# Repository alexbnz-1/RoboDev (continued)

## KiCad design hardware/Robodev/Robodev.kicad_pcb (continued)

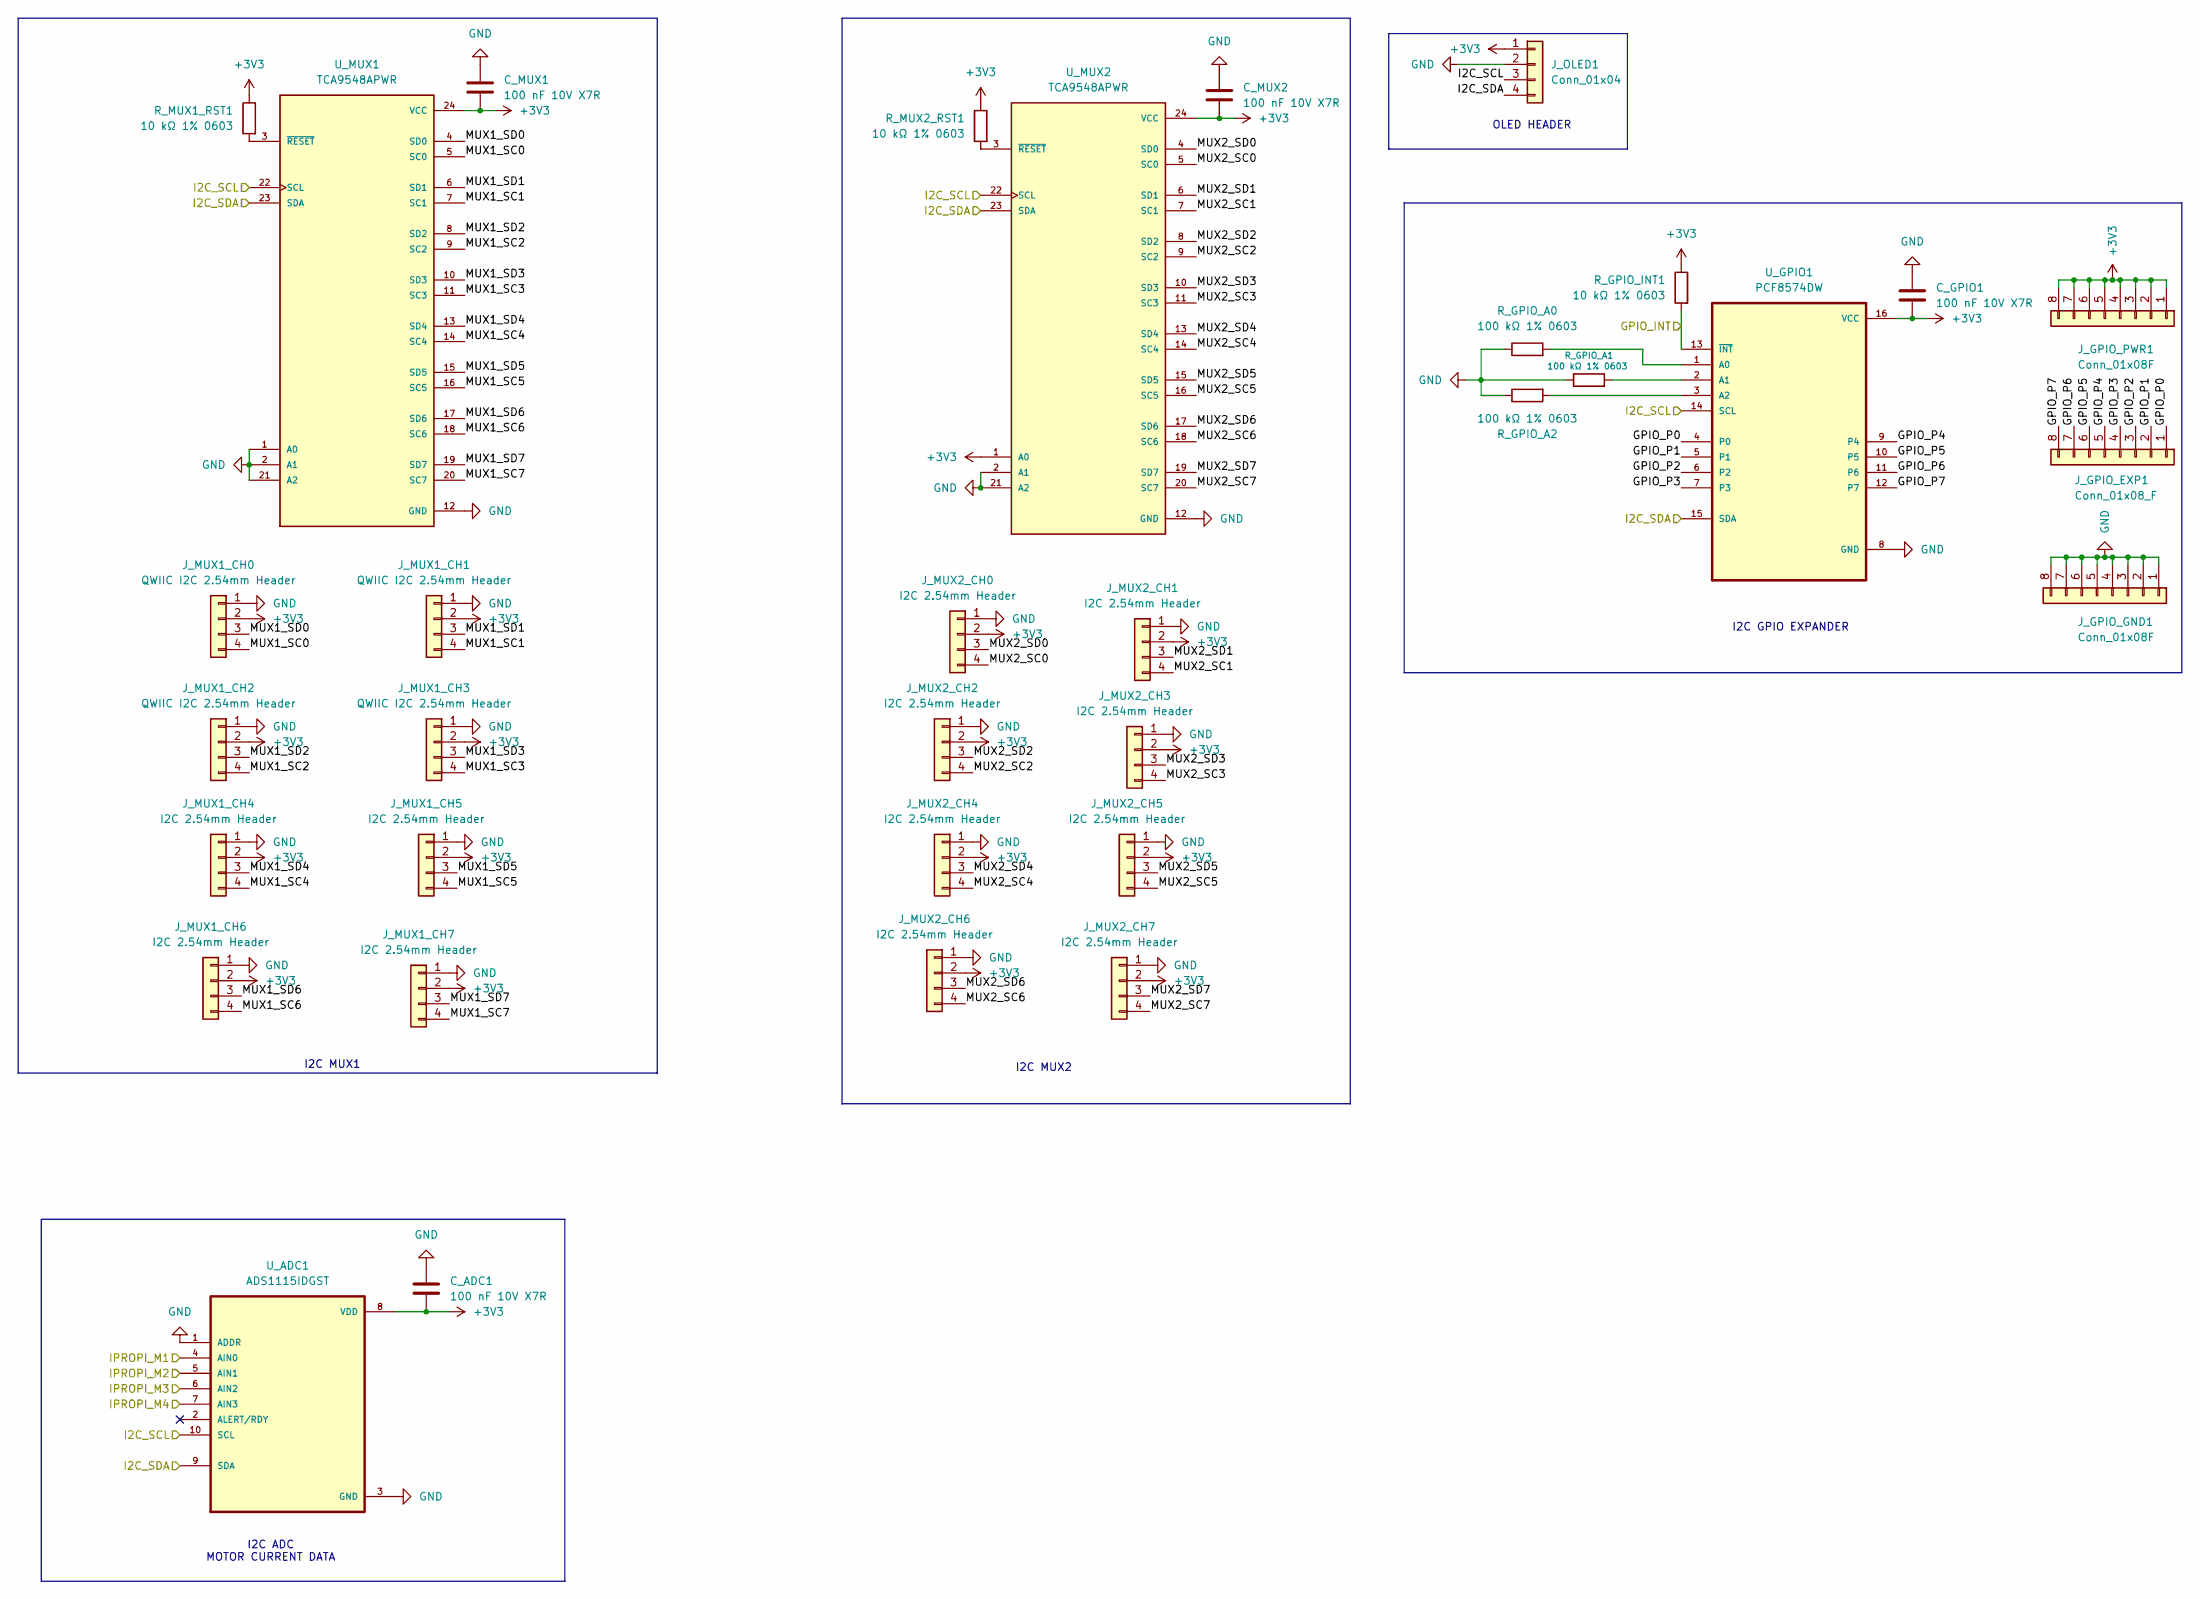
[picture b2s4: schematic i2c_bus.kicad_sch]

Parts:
C_ADC1: 100 nF 10V X7R; C_0603_1608Metric
C_GPIO1: 100 nF 10V X7R; C_0603_1608Metric
C_MUX1, C_MUX2: 100 nF 10V X7R; C_0603_1608Metric
J_GPIO_EXP1: Conn_01x08_F; PinSocket_1x08_P2.54mm_Vertical
J_GPIO_GND1: Conn_01x08F; PinSocket_1x08_P2.54mm_Vertical
J_GPIO_PWR1: Conn_01x08F; PinSocket_1x08_P2.54mm_Vertical
J_MUX1_CH0, J_MUX1_CH1, J_MUX1_CH2, J_MUX1_CH3: QWIIC I2C 2.54mm Header; ADAFRUIT_4328
J_MUX1_CH4, J_MUX1_CH5, J_MUX1_CH6, J_MUX1_CH7, J_MUX2_CH0, J_MUX2_CH1, J_MUX2_CH2, J_MUX2_CH3, J_MUX2_CH4, J_MUX2_CH5, J_MUX2_CH6, J_MUX2_CH7: I2C 2.54mm Header; PinHeader_1x04_P2.54mm_Vertical
J_OLED1: Conn_01x04; PinSocket_1x04_P2.54mm_Vertical
R_GPIO_A0, R_GPIO_A1, R_GPIO_A2: 100 kΩ 1% 0603; R_0603_1608Metric
R_GPIO_INT1: 10 kΩ 1% 0603; R_0603_1608Metric
R_MUX1_RST1, R_MUX2_RST1: 10 kΩ 1% 0603; R_0603_1608Metric
U_ADC1: ADS1115IDGST; SOP50P490X110-10N
U_GPIO1: PCF8574DW; SOIC127P1030X265-16N
U_MUX1, U_MUX2: TCA9548APWR; SOP65P640X120-24N; PARTREV G

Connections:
+3V3: C_ADC1.2, C_GPIO1.2, C_MUX1.2, C_MUX2.2, J_GPIO_PWR1.1, J_GPIO_PWR1.2, J_GPIO_PWR1.3, J_GPIO_PWR1.4, J_GPIO_PWR1.5, J_GPIO_PWR1.6, J_GPIO_PWR1.7, J_GPIO_PWR1.8, J_MUX1_CH0.2, J_MUX1_CH1.2, J_MUX1_CH2.2, J_MUX1_CH3.2, J_MUX1_CH4.2, J_MUX1_CH5.2, J_MUX1_CH6.2, J_MUX1_CH7.2, J_MUX2_CH0.2, J_MUX2_CH1.2, J_MUX2_CH2.2, J_MUX2_CH3.2, J_MUX2_CH4.2, J_MUX2_CH5.2, J_MUX2_CH6.2, J_MUX2_CH7.2, J_OLED1.1, R_GPIO_INT1.1, R_MUX1_RST1.1, R_MUX2_RST1.1, U_ADC1.8 (VDD), U_GPIO1.16 (VCC), U_MUX1.24 (VCC), U_MUX2.1 (A0), U_MUX2.24 (VCC); also elsewhere on the board
/i2c_bus/GPIO_INT: R_GPIO_INT1.2, U_GPIO1.13 (~INT); also elsewhere on the board
/i2c_bus/GPIO_P0: J_GPIO_EXP1.1, U_GPIO1.4 (P0)
/i2c_bus/GPIO_P1: J_GPIO_EXP1.2, U_GPIO1.5 (P1)
/i2c_bus/GPIO_P2: J_GPIO_EXP1.3, U_GPIO1.6 (P2)
/i2c_bus/GPIO_P3: J_GPIO_EXP1.4, U_GPIO1.7 (P3)
/i2c_bus/GPIO_P4: J_GPIO_EXP1.5, U_GPIO1.9 (P4)
/i2c_bus/GPIO_P5: J_GPIO_EXP1.6, U_GPIO1.10 (P5)
/i2c_bus/GPIO_P6: J_GPIO_EXP1.7, U_GPIO1.11 (P6)
/i2c_bus/GPIO_P7: J_GPIO_EXP1.8, U_GPIO1.12 (P7)
/i2c_bus/I2C_SCL: J_OLED1.3, U_ADC1.10 (SCL), U_GPIO1.14 (SCL), U_MUX1.22 (SCL), U_MUX2.22 (SCL); also elsewhere on the board
/i2c_bus/I2C_SDA: J_OLED1.4, U_ADC1.9 (SDA), U_GPIO1.15 (SDA), U_MUX1.23 (SDA), U_MUX2.23 (SDA); also elsewhere on the board
/i2c_bus/IPROPI_M1: U_ADC1.4 (AIN0); also elsewhere on the board
/i2c_bus/IPROPI_M2: U_ADC1.5 (AIN1); also elsewhere on the board
/i2c_bus/IPROPI_M3: U_ADC1.6 (AIN2); also elsewhere on the board
/i2c_bus/IPROPI_M4: U_ADC1.7 (AIN3); also elsewhere on the board
/i2c_bus/MUX1_SC0: J_MUX1_CH0.4, U_MUX1.5 (SC0)
/i2c_bus/MUX1_SC1: J_MUX1_CH1.4, U_MUX1.7 (SC1)
/i2c_bus/MUX1_SC2: J_MUX1_CH2.4, U_MUX1.9 (SC2)
/i2c_bus/MUX1_SC3: J_MUX1_CH3.4, U_MUX1.11 (SC3)
/i2c_bus/MUX1_SC4: J_MUX1_CH4.4, U_MUX1.14 (SC4)
/i2c_bus/MUX1_SC5: J_MUX1_CH5.4, U_MUX1.16 (SC5)
/i2c_bus/MUX1_SC6: J_MUX1_CH6.4, U_MUX1.18 (SC6)
/i2c_bus/MUX1_SC7: J_MUX1_CH7.4, U_MUX1.20 (SC7)
/i2c_bus/MUX1_SD0: J_MUX1_CH0.3, U_MUX1.4 (SD0)
/i2c_bus/MUX1_SD1: J_MUX1_CH1.3, U_MUX1.6 (SD1)
/i2c_bus/MUX1_SD2: J_MUX1_CH2.3, U_MUX1.8 (SD2)
/i2c_bus/MUX1_SD3: J_MUX1_CH3.3, U_MUX1.10 (SD3)
/i2c_bus/MUX1_SD4: J_MUX1_CH4.3, U_MUX1.13 (SD4)
/i2c_bus/MUX1_SD5: J_MUX1_CH5.3, U_MUX1.15 (SD5)
/i2c_bus/MUX1_SD6: J_MUX1_CH6.3, U_MUX1.17 (SD6)
/i2c_bus/MUX1_SD7: J_MUX1_CH7.3, U_MUX1.19 (SD7)
/i2c_bus/MUX2_SC0: J_MUX2_CH0.4, U_MUX2.5 (SC0)
/i2c_bus/MUX2_SC1: J_MUX2_CH1.4, U_MUX2.7 (SC1)
/i2c_bus/MUX2_SC2: J_MUX2_CH2.4, U_MUX2.9 (SC2)
/i2c_bus/MUX2_SC3: J_MUX2_CH3.4, U_MUX2.11 (SC3)
/i2c_bus/MUX2_SC4: J_MUX2_CH4.4, U_MUX2.14 (SC4)
/i2c_bus/MUX2_SC5: J_MUX2_CH5.4, U_MUX2.16 (SC5)
/i2c_bus/MUX2_SC6: J_MUX2_CH6.4, U_MUX2.18 (SC6)
/i2c_bus/MUX2_SC7: J_MUX2_CH7.4, U_MUX2.20 (SC7)
/i2c_bus/MUX2_SD0: J_MUX2_CH0.3, U_MUX2.4 (SD0)
/i2c_bus/MUX2_SD1: J_MUX2_CH1.3, U_MUX2.6 (SD1)
/i2c_bus/MUX2_SD2: J_MUX2_CH2.3, U_MUX2.8 (SD2)
/i2c_bus/MUX2_SD3: J_MUX2_CH3.3, U_MUX2.10 (SD3)
/i2c_bus/MUX2_SD4: J_MUX2_CH4.3, U_MUX2.13 (SD4)
/i2c_bus/MUX2_SD5: J_MUX2_CH5.3, U_MUX2.15 (SD5)
/i2c_bus/MUX2_SD6: J_MUX2_CH6.3, U_MUX2.17 (SD6)
/i2c_bus/MUX2_SD7: J_MUX2_CH7.3, U_MUX2.19 (SD7)
GND: C_ADC1.1, C_GPIO1.1, C_MUX1.1, C_MUX2.1, J_GPIO_GND1.1, J_GPIO_GND1.2, J_GPIO_GND1.3, J_GPIO_GND1.4, J_GPIO_GND1.5, J_GPIO_GND1.6, J_GPIO_GND1.7, J_GPIO_GND1.8, J_MUX1_CH0.1, J_MUX1_CH1.1, J_MUX1_CH2.1, J_MUX1_CH3.1, J_MUX1_CH4.1, J_MUX1_CH5.1, J_MUX1_CH6.1, J_MUX1_CH7.1, J_MUX2_CH0.1, J_MUX2_CH1.1, J_MUX2_CH2.1, J_MUX2_CH3.1, J_MUX2_CH4.1, J_MUX2_CH5.1, J_MUX2_CH6.1, J_MUX2_CH7.1, J_OLED1.2, R_GPIO_A0.1, R_GPIO_A1.1, R_GPIO_A2.1, U_ADC1.1 (ADDR), U_ADC1.3 (GND), U_GPIO1.8 (GND), U_MUX1.1 (A0), U_MUX1.2 (A1), U_MUX1.12 (GND), U_MUX1.21 (A2), U_MUX2.2 (A1), U_MUX2.12 (GND), U_MUX2.21 (A2); also elsewhere on the board
unnamed: R_GPIO_A0.2, U_GPIO1.1 (A0)
unnamed: R_GPIO_A1.2, U_GPIO1.2 (A1)
unnamed: R_GPIO_A2.2, U_GPIO1.3 (A2)
unnamed: R_MUX1_RST1.2, U_MUX1.3 (~RESET)
unnamed: R_MUX2_RST1.2, U_MUX2.3 (~RESET)

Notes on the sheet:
OLED HEADER
I2C GPIO EXPANDER
I2C ADC MOTOR CURRENT DATA
I2C MUX2
I2C MUX1

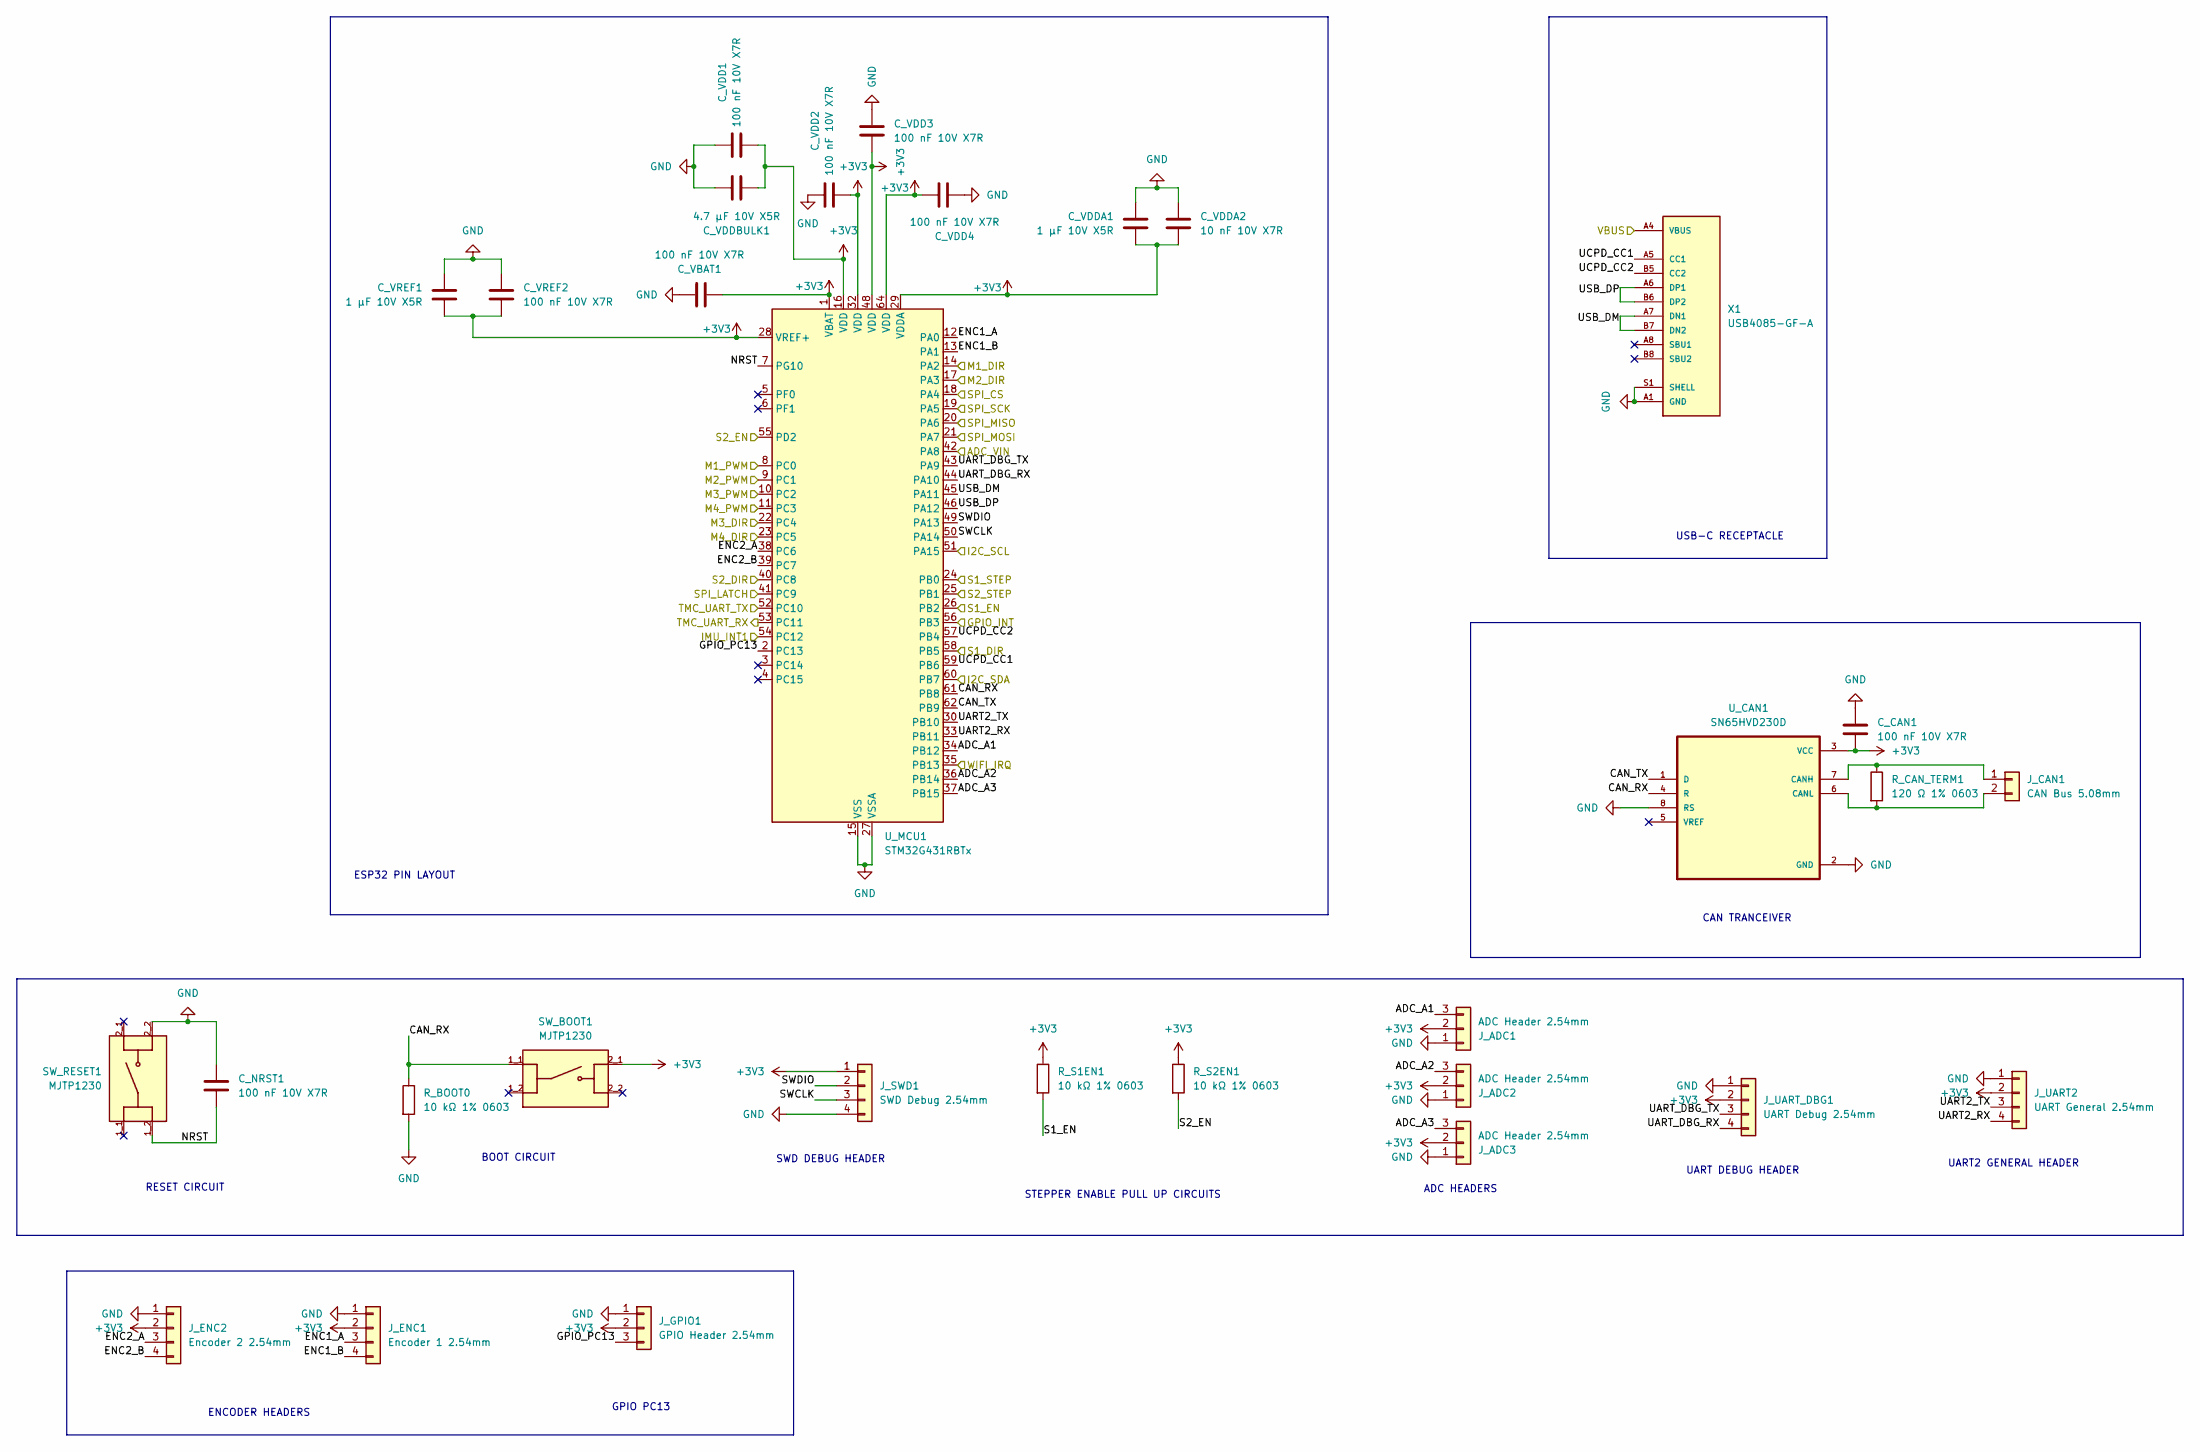
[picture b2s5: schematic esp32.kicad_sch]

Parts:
C_CAN1: 100 nF 10V X7R; C_0603_1608Metric
C_NRST1: 100 nF 10V X7R; C_0603_1608Metric
C_VBAT1: 100 nF 10V X7R; C_0603_1608Metric
C_VDD1, C_VDD2, C_VDD3, C_VDD4: 100 nF 10V X7R; C_0603_1608Metric
C_VDDA1: 1 µF 10V X5R; C_0603_1608Metric
C_VDDA2: 10 nF 10V X7R; C_0603_1608Metric
C_VDDBULK1: 4.7 µF 10V X5R; C_0603_1608Metric
C_VREF1: 1 µF 10V X5R; C_0603_1608Metric
C_VREF2: 100 nF 10V X7R; C_0603_1608Metric
J_ADC1, J_ADC2, J_ADC3: ADC Header 2.54mm; PinHeader_1x03_P2.54mm_Vertical
J_CAN1: CAN Bus 5.08mm; TerminalBlock_Phoenix_MKDS-1,5-2-5.08_1x02_P5.08mm_Horizont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
J_ENC1: Encoder 1 2.54mm; PinHeader_1x04_P2.54mm_Vertical
J_ENC2: Encoder 2 2.54mm; PinHeader_1x04_P2.54mm_Vertical
J_GPIO1: GPIO Header 2.54mm; PinSocket_1x03_P2.54mm_Vertical
J_SWD1: SWD Debug 2.54mm; FanPinHeader_1x04_P2.54mm_Vertical
J_UART2: UART General 2.54mm; PinHeader_1x04_P2.54mm_Vertical
J_UART_DBG1: UART Debug 2.54mm; PinHeader_1x04_P2.54mm_Vertical
R_BOOT0: 10 kΩ 1% 0603; R_0603_1608Metric
R_CAN_TERM1: 120 Ω 1% 0603; R_0603_1608Metric
R_S1EN1, R_S2EN1: 10 kΩ 1% 0603; R_0603_1608Metric
SW_BOOT1: MJTP1230; SW_MJTP1230; PARTREV NA
SW_RESET1: MJTP1230; SW_MJTP1230; PARTREV NA
U_CAN1: SN65HVD230D; SOIC127P599X175-8N
U_MCU1: STM32G431RBTx; LQFP-64_10x10mm_P0.5mm
X1: USB4085-GF-A; GCT_USB4085-GF-A_REVB

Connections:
+3V3: C_CAN1.2, C_VBAT1.2, C_VDD1.1, C_VDD2.1, C_VDD3.2, C_VDD4.1, C_VDDA1.2, C_VDDA2.2, C_VDDBULK1.2, C_VREF1.2, C_VREF2.2, J_ADC1.2, J_ADC2.2, J_ADC3.2, J_ENC1.2, J_ENC2.2, J_GPIO1.2, J_SWD1.1, J_UART2.2, J_UART_DBG1.2, R_S1EN1.1, R_S2EN1.1, SW_BOOT1.2_1, U_CAN1.3 (VCC), U_MCU1.1 (VBAT), U_MCU1.16 (VDD), U_MCU1.28 (VREF+), U_MCU1.29 (VDDA), U_MCU1.32 (VDD), U_MCU1.48 (VDD), U_MCU1.64 (VDD); also elsewhere on the board
/i2c_bus/GPIO_INT: U_MCU1.56 (PB3); also elsewhere on the board
/i2c_bus/I2C_SCL: U_MCU1.51 (PA15); also elsewhere on the board
/i2c_bus/I2C_SDA: U_MCU1.60 (PB7); also elsewhere on the board
/motor_dc/M1_DIR: U_MCU1.14 (PA2); also elsewhere on the board
/motor_dc/M1_PWM: U_MCU1.8 (PC0); also elsewhere on the board
/motor_dc/M2_DIR: U_MCU1.17 (PA3); also elsewhere on the board
/motor_dc/M2_PWM: U_MCU1.9 (PC1); also elsewhere on the board
/motor_dc/M3_DIR: U_MCU1.22 (PC4); also elsewhere on the board
/motor_dc/M3_PWM: U_MCU1.10 (PC2); also elsewhere on the board
/motor_dc/M4_DIR: U_MCU1.23 (PC5); also elsewhere on the board
/motor_dc/M4_PWM: U_MCU1.11 (PC3); also elsewhere on the board
/motor_stepper/S1_DIR: U_MCU1.58 (PB5); also elsewhere on the board
/motor_stepper/S1_STEP: U_MCU1.24 (PB0); also elsewhere on the board
/motor_stepper/S2_DIR: U_MCU1.40 (PC8); also elsewhere on the board
/motor_stepper/S2_STEP: U_MCU1.25 (PB1); also elsewhere on the board
/motor_stepper/TMC_UART: U_MCU1.52 (PC10), U_MCU1.53 (PC11); also elsewhere on the board
/power/ADC_VIN: U_MCU1.42 (PA8); also elsewhere on the board
/spi_bus/IMU_INT1: U_MCU1.54 (PC12); also elsewhere on the board
/spi_bus/SPI_CS: U_MCU1.18 (PA4); also elsewhere on the board
/spi_bus/SPI_LATCH: U_MCU1.41 (PC9); also elsewhere on the board
/spi_bus/SPI_MISO: U_MCU1.20 (PA6); also elsewhere on the board
/spi_bus/SPI_MOSI: U_MCU1.21 (PA7); also elsewhere on the board
/spi_bus/SPI_SCK: U_MCU1.19 (PA5); also elsewhere on the board
/spi_bus/WIFI_IRQ: U_MCU1.35 (PB13); also elsewhere on the board
/stm32/ADC_A1: J_ADC1.3, U_MCU1.34 (PB12)
/stm32/ADC_A2: J_ADC2.3, U_MCU1.36 (PB14)
/stm32/ADC_A3: J_ADC3.3, U_MCU1.37 (PB15)
/stm32/CAN_RX: R_BOOT0.1, SW_BOOT1.1_1, U_CAN1.4 (R), U_MCU1.61 (PB8)
/stm32/CAN_TX: U_CAN1.1 (D), U_MCU1.62 (PB9)
/stm32/ENC1_A: J_ENC1.3, U_MCU1.12 (PA0)
/stm32/ENC1_B: J_ENC1.4, U_MCU1.13 (PA1)
/stm32/ENC2_A: J_ENC2.3, U_MCU1.38 (PC6)
/stm32/ENC2_B: J_ENC2.4, U_MCU1.39 (PC7)
/stm32/GPIO_PC13: J_GPIO1.3, U_MCU1.2 (PC13)
/stm32/NRST: C_NRST1.2, SW_RESET1.1_2, U_MCU1.7 (PG10)
/stm32/S1_EN: R_S1EN1.2, U_MCU1.26 (PB2); also elsewhere on the board
/stm32/S2_EN: R_S2EN1.2, U_MCU1.55 (PD2); also elsewhere on the board
/stm32/SWCLK: J_SWD1.3, U_MCU1.50 (PA14)
/stm32/SWDIO: J_SWD1.2, U_MCU1.49 (PA13)
/stm32/UART2_RX: J_UART2.4, U_MCU1.33 (PB11)
/stm32/UART2_TX: J_UART2.3, U_MCU1.30 (PB10)
/stm32/UART_DBG_RX: J_UART_DBG1.4, U_MCU1.44 (PA10)
/stm32/UART_DBG_TX: J_UART_DBG1.3, U_MCU1.43 (PA9)
/stm32/UCPD_CC1: U_MCU1.59 (PB6), X1.A5 (CC1)
/stm32/UCPD_CC2: U_MCU1.57 (PB4), X1.B5 (CC2)
/stm32/USB_DM: U_MCU1.45 (PA11), X1.A7 (DN1), X1.B7 (DN2)
/stm32/USB_DP: U_MCU1.46 (PA12), X1.A6 (DP1), X1.B6 (DP2)
GND: C_CAN1.1, C_NRST1.1, C_VBAT1.1, C_VDD1.2, C_VDD2.2, C_VDD3.1, C_VDD4.2, C_VDDA1.1, C_VDDA2.1, C_VDDBULK1.1, C_VREF1.1, C_VREF2.1, J_ADC1.1, J_ADC2.1, J_ADC3.1, J_ENC1.1, J_ENC2.1, J_GPIO1.1, J_SWD1.4, J_UART2.1, J_UART_DBG1.1, R_BOOT0.2, SW_RESET1.2_2, U_CAN1.2 (GND), U_CAN1.8 (RS), U_MCU1.15 (VSS), U_MCU1.27 (VSSA), U_MCU1.31 (VSS), U_MCU1.47 (VSS), U_MCU1.63 (VSS), X1.A1 (GND), X1.A12 (GND), X1.B1 (GND), X1.B12 (GND), X1.S1 (SHELL), X1.S2 (SHELL), X1.S3 (SHELL), X1.S4 (SHELL); also elsewhere on the board
unnamed: J_CAN1.1, R_CAN_TERM1.1, U_CAN1.7 (CANH)
unnamed: J_CAN1.2, R_CAN_TERM1.2, U_CAN1.6 (CANL)
VBUS: X1.A4 (VBUS), X1.A9 (VBUS), X1.B4 (VBUS), X1.B9 (VBUS); also elsewhere on the board

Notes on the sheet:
BOOT CIRCUIT
SWD DEBUG HEADER
ENCODER HEADERS
CAN TRANCEIVER
GPIO PC13
RESET CIRCUIT
STEPPER ENABLE PULL UP CIRCUITS
UART2 GENERAL HEADER
ESP32 PIN LAYOUT
UART DEBUG HEADER
USB-C RECEPTACLE
ADC HEADERS

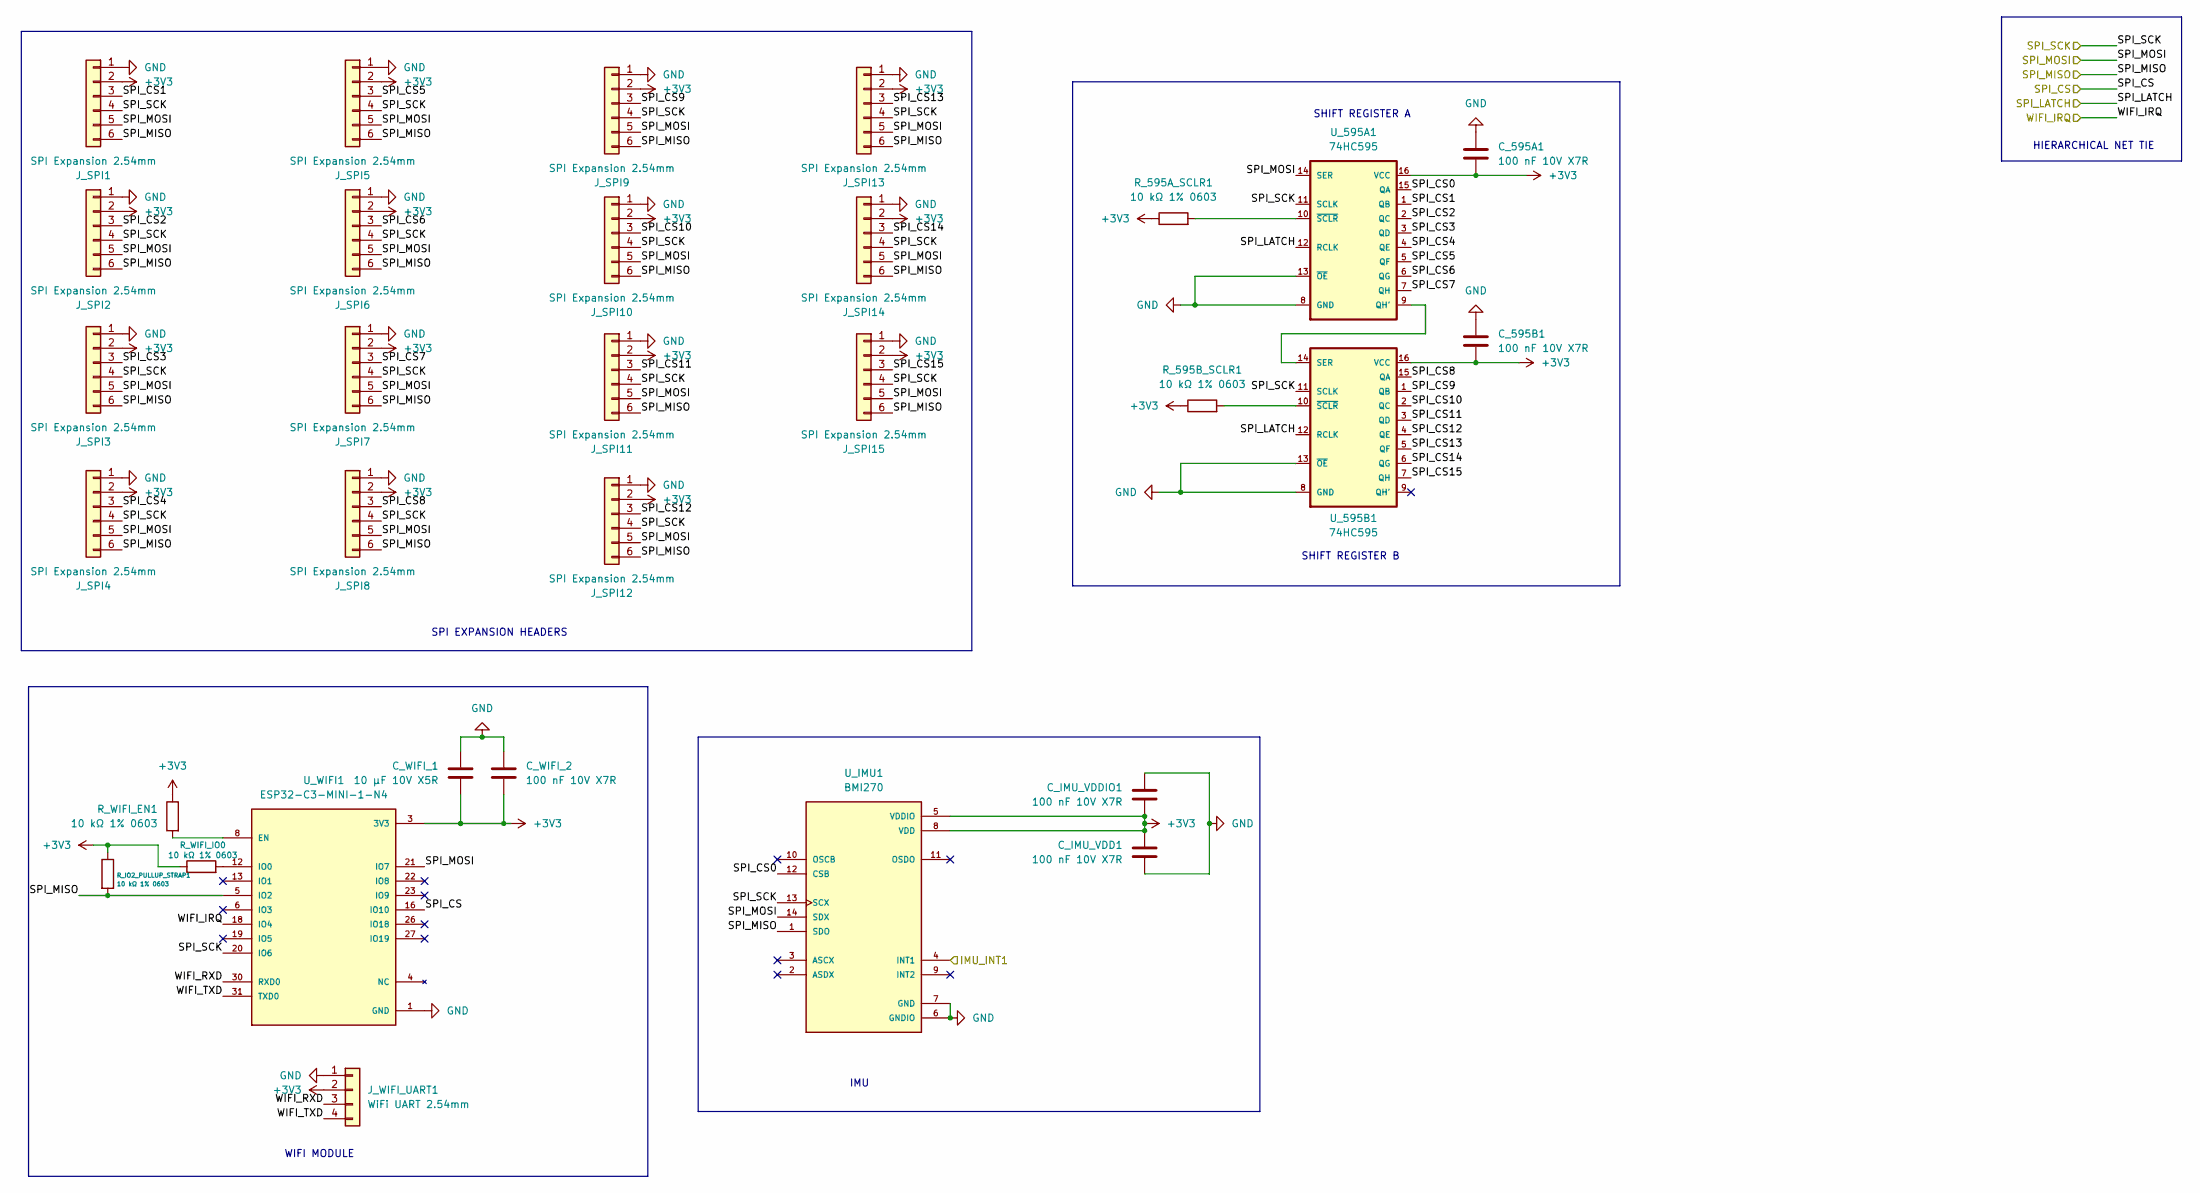
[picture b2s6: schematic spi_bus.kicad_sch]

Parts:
C_595A1, C_595B1: 100 nF 10V X7R; C_0603_1608Metric
C_IMU_VDD1: 100 nF 10V X7R; C_0603_1608Metric
C_IMU_VDDIO1: 100 nF 10V X7R; C_0603_1608Metric
C_WIFI_1: 10 µF 10V X5R; C_0603_1608Metric
C_WIFI_2: 100 nF 10V X7R; C_0603_1608Metric
J_SPI1, J_SPI2, J_SPI3, J_SPI4, J_SPI5, J_SPI6, J_SPI7, J_SPI8, J_SPI9, J_SPI10, J_SPI11, J_SPI12, J_SPI13, J_SPI14, J_SPI15: SPI Expansion 2.54mm; PinHeader_1x06_P2.54mm_Vertical
J_WIFI_UART1: WiFi UART 2.54mm; PinHeader_1x04_P2.54mm_Vertical
R_595A_SCLR1, R_595B_SCLR1: 10 kΩ 1% 0603; R_0603_1608Metric
R_IO2_PULLUP_STRAP1: 10 kΩ 1% 0603; R_0603_1608Metric
R_WIFI_EN1: 10 kΩ 1% 0603; R_0603_1608Metric
R_WIFI_IO0: 10 kΩ 1% 0603; R_0603_1608Metric
U_595A1, U_595B1: 74HC595; SO16
U_IMU1: BMI270; XDCR_BMI270
U_WIFI1: ESP32-C3-MINI-1-N4; XCVR_ESP32-C3-MINI-1-N4; PARTREV v1.0

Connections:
+3V3: C_595A1.2, C_595B1.2, C_IMU_VDD1.1, C_IMU_VDDIO1.2, C_WIFI_1.2, C_WIFI_2.2, J_SPI1.2, J_SPI2.2, J_SPI3.2, J_SPI4.2, J_SPI5.2, J_SPI6.2, J_SPI7.2, J_SPI8.2, J_SPI9.2, J_SPI10.2, J_SPI11.2, J_SPI12.2, J_SPI13.2, J_SPI14.2, J_SPI15.2, J_WIFI_UART1.2, R_595A_SCLR1.1, R_595B_SCLR1.1, R_IO2_PULLUP_STRAP1.1, R_WIFI_EN1.1, R_WIFI_IO0.1, U_595A1.16 (VCC), U_595B1.16 (VCC), U_IMU1.5 (VDDIO), U_IMU1.8 (VDD), U_WIFI1.3 (3V3); also elsewhere on the board
/spi_bus/IMU_INT1: U_IMU1.4 (INT1); also elsewhere on the board
/spi_bus/SPI_CS: U_WIFI1.16 (IO10); also elsewhere on the board
/spi_bus/SPI_CS0: U_595A1.15 (QA), U_IMU1.12 (CSB)
/spi_bus/SPI_CS1: J_SPI1.3, U_595A1.1 (QB)
/spi_bus/SPI_CS2: J_SPI2.3, U_595A1.2 (QC)
/spi_bus/SPI_CS3: J_SPI3.3, U_595A1.3 (QD)
/spi_bus/SPI_CS4: J_SPI4.3, U_595A1.4 (QE)
/spi_bus/SPI_CS5: J_SPI5.3, U_595A1.5 (QF)
/spi_bus/SPI_CS6: J_SPI6.3, U_595A1.6 (QG)
/spi_bus/SPI_CS7: J_SPI7.3, U_595A1.7 (QH)
/spi_bus/SPI_CS8: J_SPI8.3, U_595B1.15 (QA)
/spi_bus/SPI_CS9: J_SPI9.3, U_595B1.1 (QB)
/spi_bus/SPI_CS10: J_SPI10.3, U_595B1.2 (QC)
/spi_bus/SPI_CS11: J_SPI11.3, U_595B1.3 (QD)
/spi_bus/SPI_CS12: J_SPI12.3, U_595B1.4 (QE)
/spi_bus/SPI_CS13: J_SPI13.3, U_595B1.5 (QF)
/spi_bus/SPI_CS14: J_SPI14.3, U_595B1.6 (QG)
/spi_bus/SPI_CS15: J_SPI15.3, U_595B1.7 (QH)
/spi_bus/SPI_LATCH: U_595A1.12 (RCLK), U_595B1.12 (RCLK); also elsewhere on the board
/spi_bus/SPI_MISO: J_SPI1.6, J_SPI2.6, J_SPI3.6, J_SPI4.6, J_SPI5.6, J_SPI6.6, J_SPI7.6, J_SPI8.6, J_SPI9.6, J_SPI10.6, J_SPI11.6, J_SPI12.6, J_SPI13.6, J_SPI14.6, J_SPI15.6, R_IO2_PULLUP_STRAP1.2, U_IMU1.1 (SDO), U_WIFI1.5 (IO2); also elsewhere on the board
/spi_bus/SPI_MOSI: J_SPI1.5, J_SPI2.5, J_SPI3.5, J_SPI4.5, J_SPI5.5, J_SPI6.5, J_SPI7.5, J_SPI8.5, J_SPI9.5, J_SPI10.5, J_SPI11.5, J_SPI12.5, J_SPI13.5, J_SPI14.5, J_SPI15.5, U_595A1.14 (SER), U_IMU1.14 (SDX), U_WIFI1.21 (IO7); also elsewhere on the board
/spi_bus/SPI_SCK: J_SPI1.4, J_SPI2.4, J_SPI3.4, J_SPI4.4, J_SPI5.4, J_SPI6.4, J_SPI7.4, J_SPI8.4, J_SPI9.4, J_SPI10.4, J_SPI11.4, J_SPI12.4, J_SPI13.4, J_SPI14.4, J_SPI15.4, U_595A1.11 (SCLK), U_595B1.11 (SCLK), U_IMU1.13 (SCX), U_WIFI1.20 (IO6); also elsewhere on the board
/spi_bus/WIFI_IRQ: U_WIFI1.18 (IO4); also elsewhere on the board
/spi_bus/WIFI_RXD: J_WIFI_UART1.3, U_WIFI1.30 (RXD0)
/spi_bus/WIFI_TXD: J_WIFI_UART1.4, U_WIFI1.31 (TXD0)
GND: C_595A1.1, C_595B1.1, C_IMU_VDD1.2, C_IMU_VDDIO1.1, C_WIFI_1.1, C_WIFI_2.1, J_SPI1.1, J_SPI2.1, J_SPI3.1, J_SPI4.1, J_SPI5.1, J_SPI6.1, J_SPI7.1, J_SPI8.1, J_SPI9.1, J_SPI10.1, J_SPI11.1, J_SPI12.1, J_SPI13.1, J_SPI14.1, J_SPI15.1, J_WIFI_UART1.1, U_595A1.8 (GND), U_595A1.13 (~OE), U_595B1.8 (GND), U_595B1.13 (~OE), U_IMU1.6 (GNDIO), U_IMU1.7 (GND), U_WIFI1.1 (GND), U_WIFI1.2 (GND), U_WIFI1.11 (GND), U_WIFI1.14 (GND), U_WIFI1.36 (GND), U_WIFI1.37 (GND), U_WIFI1.38 (GND), U_WIFI1.39 (GND), U_WIFI1.40 (GND), U_WIFI1.41 (GND), U_WIFI1.42 (GND), U_WIFI1.43 (GND), U_WIFI1.44 (GND), U_WIFI1.45 (GND), U_WIFI1.46 (GND), U_WIFI1.47 (GND), U_WIFI1.48 (GND), U_WIFI1.49_1 (GND), U_WIFI1.49_2 (GND), U_WIFI1.49_3 (GND), U_WIFI1.49_4 (GND), U_WIFI1.49_5 (GND), U_WIFI1.49_6 (GND), U_WIFI1.49_7 (GND), U_WIFI1.49_8 (GND), U_WIFI1.49_9 (GND), U_WIFI1.50 (GND), U_WIFI1.51 (GND), U_WIFI1.52 (GND), U_WIFI1.53 (GND); also elsewhere on the board
unnamed: U_595A1.9 (QH'), U_595B1.14 (SER)
unnamed: R_595A_SCLR1.2, U_595A1.10 (~SCLR)
unnamed: R_595B_SCLR1.2, U_595B1.10 (~SCLR)
unnamed: R_WIFI_EN1.2, U_WIFI1.8 (EN)
unnamed: R_WIFI_IO0.2, U_WIFI1.12 (IO0)

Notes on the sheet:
SHIFT REGISTER B
HIERARCHICAL NET TIE
SHIFT REGISTER A
SPI EXPANSION HEADERS
WIFI MODULE
IMU

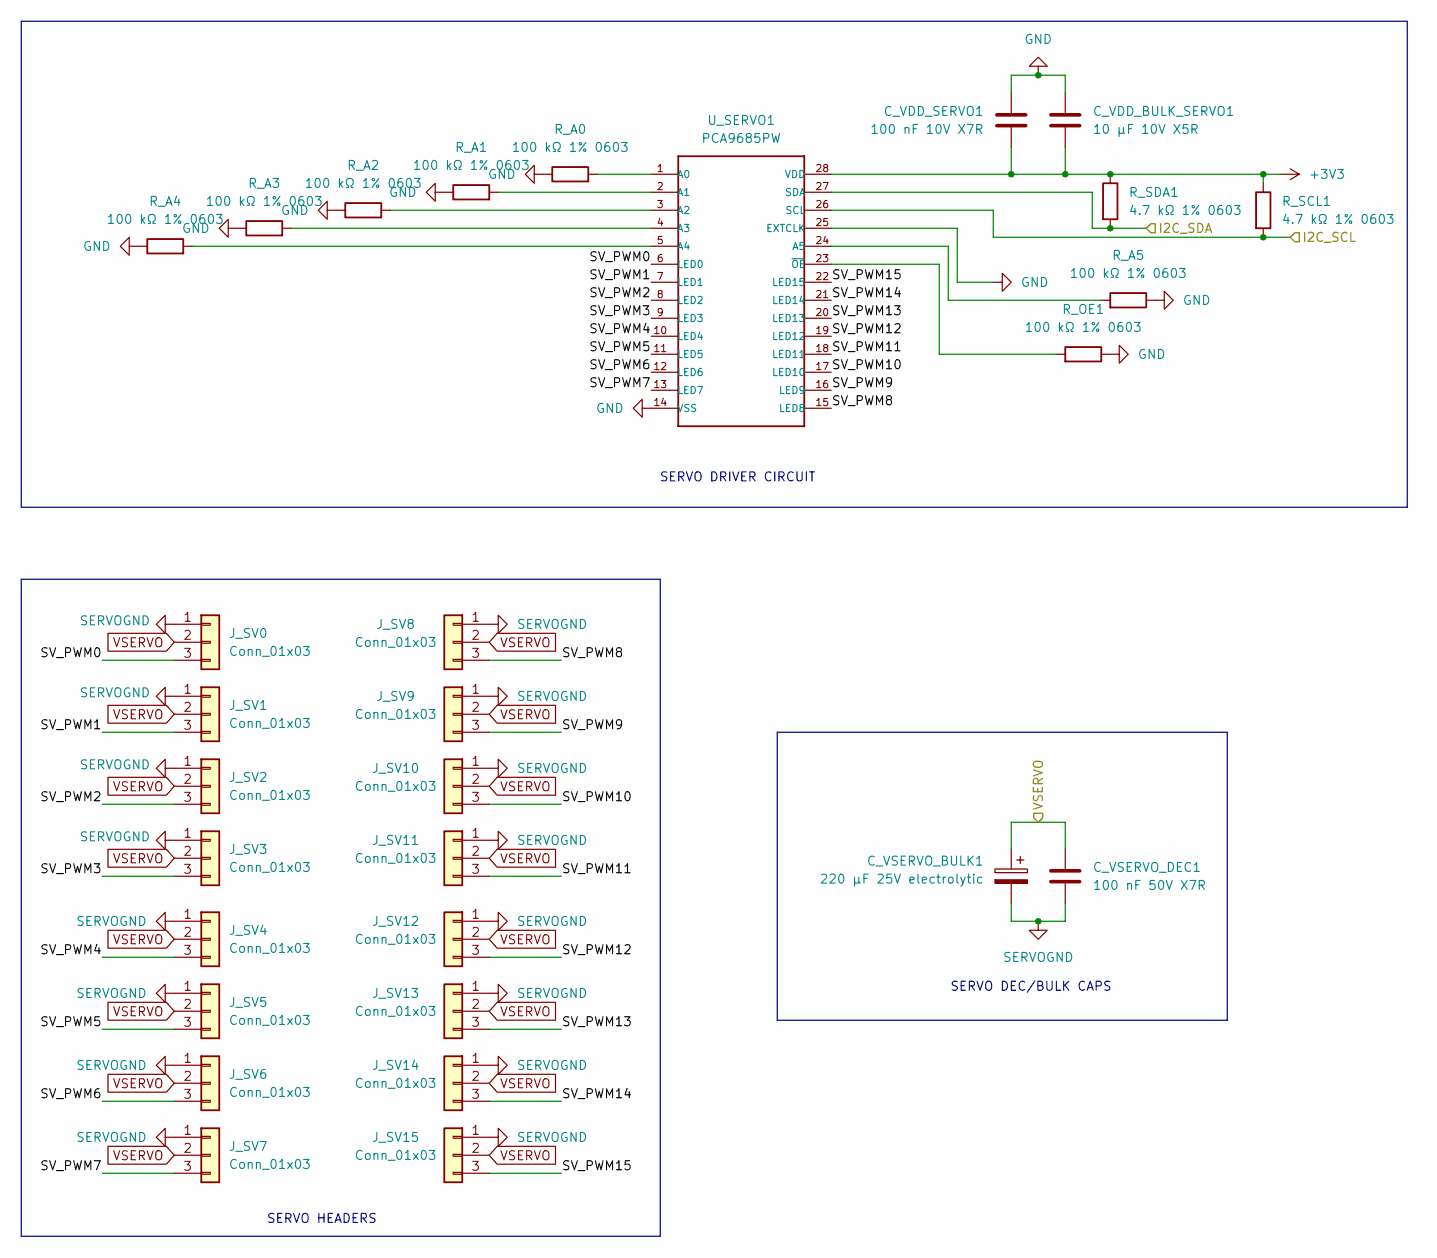
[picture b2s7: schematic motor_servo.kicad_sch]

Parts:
C_VDD_BULK_SERVO1: 10 µF 10V X5R; C_0603_1608Metric
C_VDD_SERVO1: 100 nF 10V X7R; C_0603_1608Metric
C_VSERVO_BULK1: 220 µF 25V electrolytic; CP_Radial_D8.0mm_P3.50mm
C_VSERVO_DEC1: 100 nF 50V X7R; C_0603_1608Metric
J_SV0, J_SV1, J_SV2, J_SV3, J_SV4, J_SV5, J_SV6, J_SV7, J_SV8, J_SV9, J_SV10, J_SV11, J_SV12, J_SV13, J_SV14, J_SV15: Conn_01x03; PinHeader_1x03_P2.54mm_Vertical
R_A0, R_A1, R_A2, R_A3, R_A4, R_A5: 100 kΩ 1% 0603; R_0603_1608Metric
R_OE1: 100 kΩ 1% 0603; R_0603_1608Metric
R_SCL1: 4.7 kΩ 1% 0603; R_0603_1608Metric
R_SDA1: 4.7 kΩ 1% 0603; R_0603_1608Metric
U_SERVO1: PCA9685PW; TSSOP28-0.65-9.7X4.4MM; MPN PCA9685PW

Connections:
+3V3: C_VDD_BULK_SERVO1.2, C_VDD_SERVO1.2, R_SCL1.1, R_SDA1.1, U_SERVO1.28 (VDD); also elsewhere on the board
/i2c_bus/I2C_SCL: R_SCL1.2, U_SERVO1.26 (SCL); also elsewhere on the board
/i2c_bus/I2C_SDA: R_SDA1.2, U_SERVO1.27 (SDA); also elsewhere on the board
/motor_servo/SV_PWM0: J_SV0.3, U_SERVO1.6 (LED0)
/motor_servo/SV_PWM1: J_SV1.3, U_SERVO1.7 (LED1)
/motor_servo/SV_PWM2: J_SV2.3, U_SERVO1.8 (LED2)
/motor_servo/SV_PWM3: J_SV3.3, U_SERVO1.9 (LED3)
/motor_servo/SV_PWM4: J_SV4.3, U_SERVO1.10 (LED4)
/motor_servo/SV_PWM5: J_SV5.3, U_SERVO1.11 (LED5)
/motor_servo/SV_PWM6: J_SV6.3, U_SERVO1.12 (LED6)
/motor_servo/SV_PWM7: J_SV7.3, U_SERVO1.13 (LED7)
/motor_servo/SV_PWM8: J_SV8.3, U_SERVO1.15 (LED8)
/motor_servo/SV_PWM9: J_SV9.3, U_SERVO1.16 (LED9)
/motor_servo/SV_PWM10: J_SV10.3, U_SERVO1.17 (LED10)
/motor_servo/SV_PWM11: J_SV11.3, U_SERVO1.18 (LED11)
/motor_servo/SV_PWM12: J_SV12.3, U_SERVO1.19 (LED12)
/motor_servo/SV_PWM13: J_SV13.3, U_SERVO1.20 (LED13)
/motor_servo/SV_PWM14: J_SV14.3, U_SERVO1.21 (LED14)
/motor_servo/SV_PWM15: J_SV15.3, U_SERVO1.22 (LED15)
GND: C_VDD_BULK_SERVO1.1, C_VDD_SERVO1.1, R_A0.1, R_A1.1, R_A2.1, R_A3.1, R_A4.1, R_A5.1, R_OE1.1, U_SERVO1.14 (VSS), U_SERVO1.25 (EXTCLK); also elsewhere on the board
unnamed: R_A0.2, U_SERVO1.1 (A0)
unnamed: R_A1.2, U_SERVO1.2 (A1)
unnamed: R_A2.2, U_SERVO1.3 (A2)
unnamed: R_A3.2, U_SERVO1.4 (A3)
unnamed: R_A4.2, U_SERVO1.5 (A4)
unnamed: R_A5.2, U_SERVO1.24 (A5)
unnamed: R_OE1.2, U_SERVO1.23 (~OE)
SERVOGND: C_VSERVO_BULK1.2, C_VSERVO_DEC1.2, J_SV0.1, J_SV1.1, J_SV2.1, J_SV3.1, J_SV4.1, J_SV5.1, J_SV6.1, J_SV7.1, J_SV8.1, J_SV9.1, J_SV10.1, J_SV11.1, J_SV12.1, J_SV13.1, J_SV14.1, J_SV15.1; also elsewhere on the board
VSERVO: C_VSERVO_BULK1.1, C_VSERVO_DEC1.1, J_SV0.2, J_SV1.2, J_SV2.2, J_SV3.2, J_SV4.2, J_SV5.2, J_SV6.2, J_SV7.2, J_SV8.2, J_SV9.2, J_SV10.2, J_SV11.2, J_SV12.2, J_SV13.2, J_SV14.2, J_SV15.2; also elsewhere on the board

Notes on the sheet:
SERVO DRIVER CIRCUIT
SERVO DEC/BULK CAPS
SERVO HEADERS
